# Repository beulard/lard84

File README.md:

# lard84

A custom 75% ansi low-profile keyboard.

- [PCB](#pcb)
- [Plate](#plate)
- [Case](#case)
- [Acknowledgments](#acknowledgments)
- [Extra pictures](#extra-pictures)

The assembly is done in (sort of) [sandwich mount style](https://thomasbaart.nl/2019/04/07/cheat-sheet-custom-keyboard-mounting-styles/).
Compared to sandwich mount, there is no top frame (the plate sits at the top), and
it is screwed into the case's mounting posts from above.

Here it is finally assembled:

## PCB

The PCB (lard84.kicad_pro) is an 84-key design based on the [RP2350 Stamp](https://lectronz.com/products/rp2350-stamp), made using KiCad 8.0.
It is entirely hand-solderable (smallest footprint is 0603).

The design features a micro-usb port, full n-key rollover using a diode for each switch, a status LED, and apparent debug pins for development.

Key placement follows an [ANSI 75% layout](https://docs.keebd.com/information/keyboard-layouts#75-ansi).

The design supports [Gateron KS-33 low-profile switches](https://www.gateron.co/products/gateron-low-profile-mechanical-switch-set), and features holes
for the associated [low-profile stabilizers](https://www.gateron.com/products/gateron-low-profile-plate-mounted-stabilizer).

## Plate

The top plate (plate v38.f3z) supports the switches, adds rigidity and gives a nice finish. It was made in Fusion360.

It is a relatively simple design with a square cutout for each key, two extra cutouts around the Backspace, Space, Enter and LShift keys
for their plate-mounted stabilizers, and 10 mounting holes for screws.

One key challenge was to figure out the placement and shape for the stabilizer cutouts, because of insufficient information on
the datasheets from the manufacturer.

## Case

The case (case.FCStd) is a 3D-printable plastic enclosing and two feet for a more comfortable typing angle.

The enclosing features mounting posts for the PCB and plate, and anti-warping structural elements.

## Acknowledgments

Thanks to these open source repos for providing vital KiCad symbol/footprint libraries.
- [RP2350 Stamp](https://github.com/solderparty/rp2xxx_stamp_footprints)
- [Gateron switches](https://github.com/siderakb/key-switches.pretty)

## Extra pictures

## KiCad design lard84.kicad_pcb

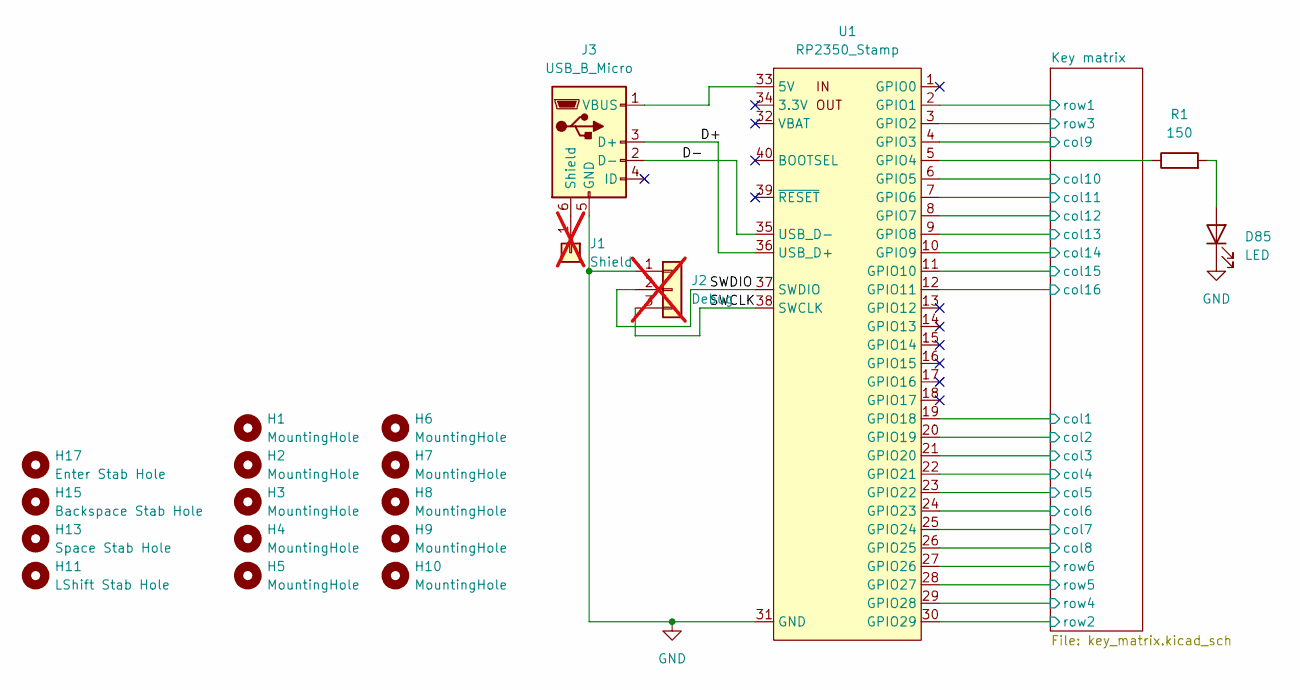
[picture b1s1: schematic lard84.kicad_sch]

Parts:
D85: LED; LED_0603_1608Metric_Pad1.05x0.95mm_HandSolder
H1, H2, H3, H4, H5, H6, H7, H8, H9, H10: MountingHole; Stand hole 5mm
H11: LShift Stab Hole; Gateron low-profile 2U stabilizer
H13: Space Stab Hole; Gateron low-profile 6.25U stabilizer
H15: Backspace Stab Hole; Gateron low-profile 2U stabilizer
H17: Enter Stab Hole; Gateron low-profile 2U stabilizer
J1: Shield; PinSocket_1x01_P2.00mm_Vertical; not fitted
J2: Debug; PinSocket_1x03_P2.54mm_Vertical; not fitted
J3: USB_B_Micro; CONN5_2013499-1_TEC
R1: 150; R_0603_1608Metric_Pad0.98x0.95mm_HandSolder
U1: RP2350_Stamp; RP2xxx_Stamp_SMD

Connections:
/D+: J3.3 (D+), U1.36 (USB_D+)
/D-: J3.2 (D-), U1.35 (USB_D-)
/Key matrix/col1: U1.19 (GPIO18); also elsewhere on the board
/Key matrix/col2: U1.20 (GPIO19); also elsewhere on the board
/Key matrix/col3: U1.21 (GPIO20); also elsewhere on the board
/Key matrix/col4: U1.22 (GPIO21); also elsewhere on the board
/Key matrix/col5: U1.23 (GPIO22); also elsewhere on the board
/Key matrix/col6: U1.24 (GPIO23); also elsewhere on the board
/Key matrix/col7: U1.25 (GPIO24); also elsewhere on the board
/Key matrix/col8: U1.26 (GPIO25); also elsewhere on the board
/Key matrix/col9: U1.4 (GPIO3); also elsewhere on the board
/Key matrix/col10: U1.6 (GPIO5); also elsewhere on the board
/Key matrix/col11: U1.7 (GPIO6); also elsewhere on the board
/Key matrix/col12: U1.8 (GPIO7); also elsewhere on the board
/Key matrix/col13: U1.9 (GPIO8); also elsewhere on the board
/Key matrix/col14: U1.10 (GPIO9); also elsewhere on the board
/Key matrix/col15: U1.11 (GPIO10); also elsewhere on the board
/Key matrix/col16: U1.12 (GPIO11); also elsewhere on the board
/Key matrix/row1: U1.2 (GPIO1); also elsewhere on the board
/Key matrix/row2: U1.30 (GPIO29); also elsewhere on the board
/Key matrix/row3: U1.3 (GPIO2); also elsewhere on the board
/Key matrix/row4: U1.29 (GPIO28); also elsewhere on the board
/Key matrix/row5: U1.28 (GPIO27); also elsewhere on the board
/Key matrix/row6: U1.27 (GPIO26); also elsewhere on the board
/SWCLK: J2.3, U1.38 (SWCLK)
/SWDIO: J2.2, U1.37 (SWDIO)
GND: D85.1 (K), J2.1, J3.5 (GND), U1.31 (GND)
unnamed: D85.2 (A), R1.2
unnamed: J1.1, J3.6 (Shield)
unnamed: J3.1 (VBUS), U1.33 (5V)
unnamed: R1.1, U1.5 (GPIO4)

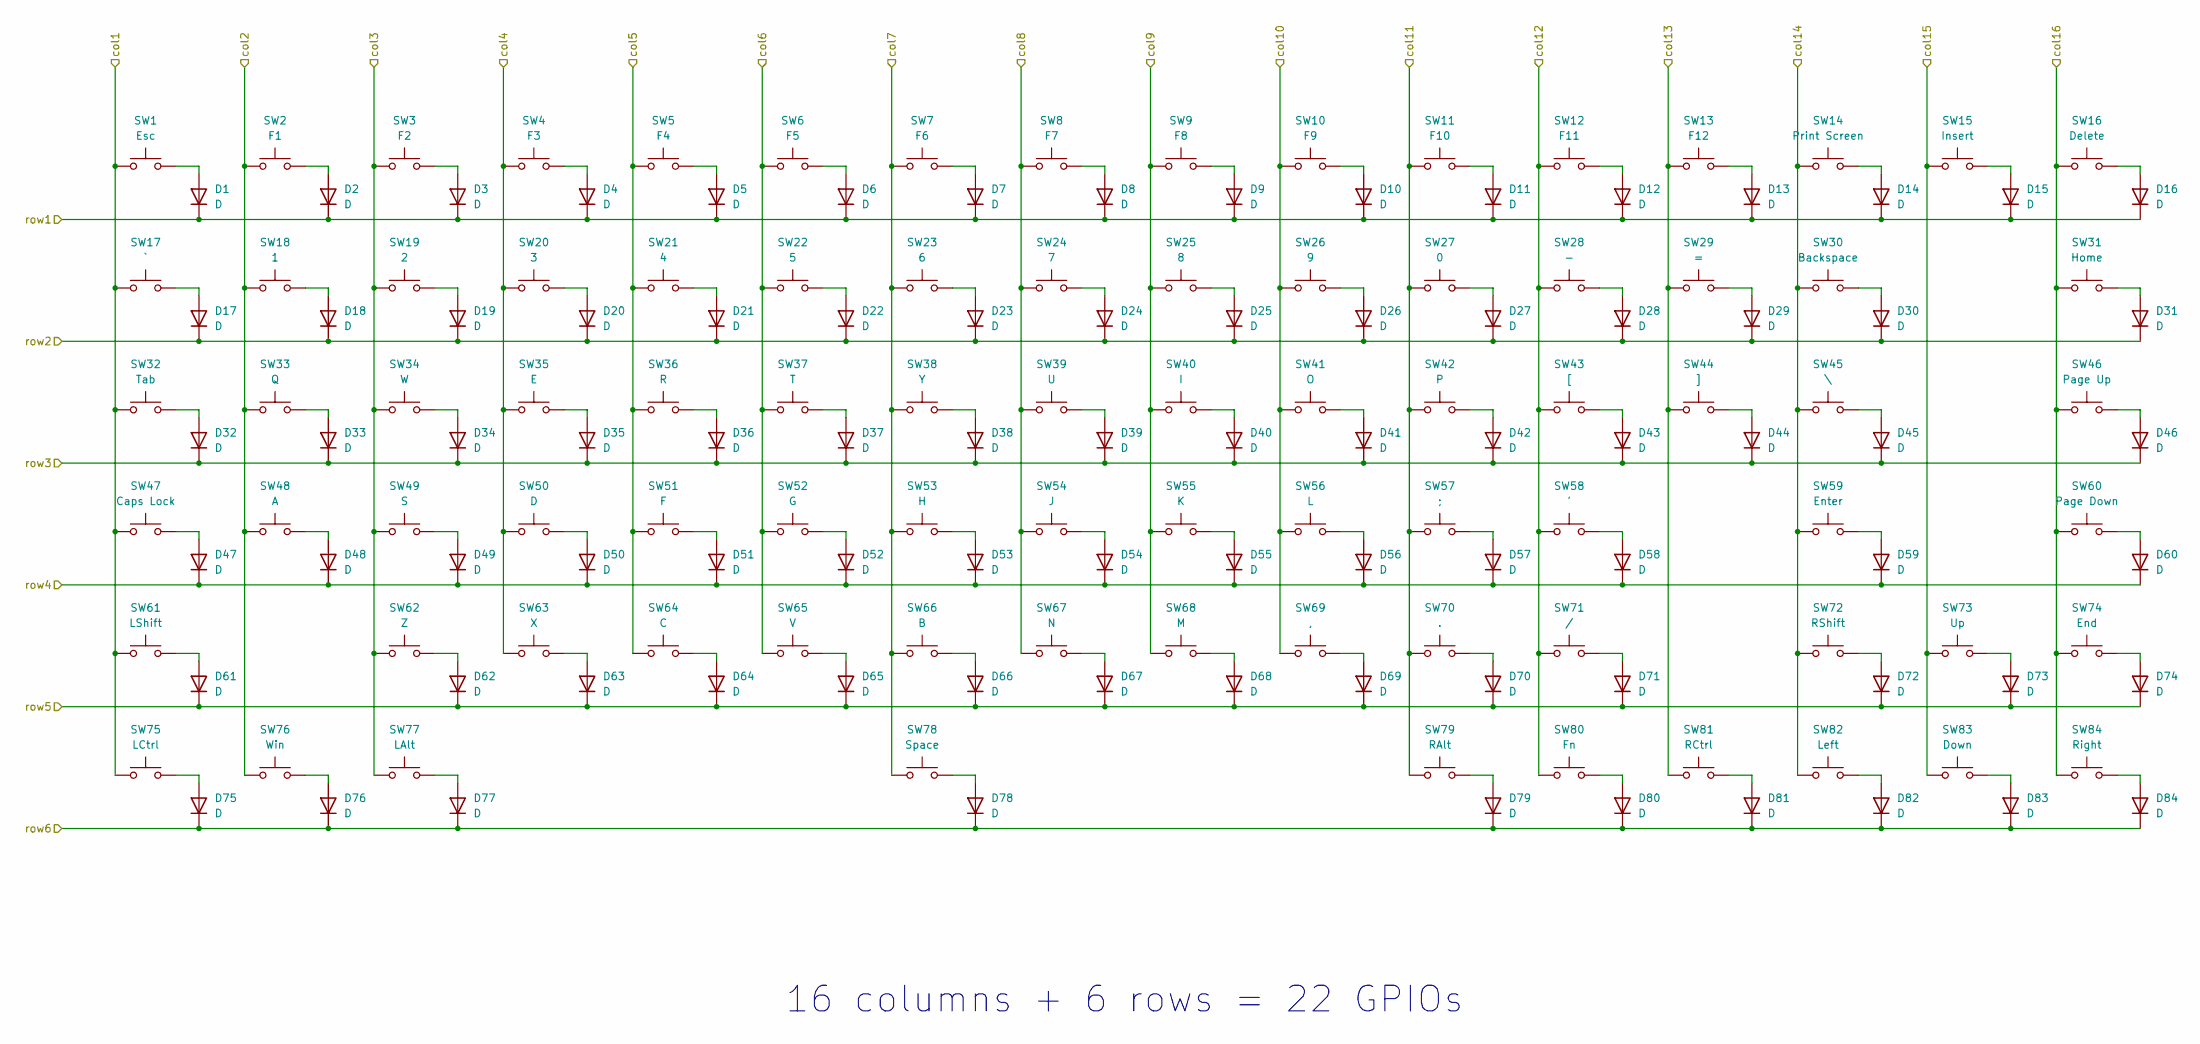
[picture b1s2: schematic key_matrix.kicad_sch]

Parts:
D1, D2, D3, D4, D5, D6, D7, D8, D9, D10, D11, D12, D13, D14, D15, D16, D17, D18, D19, D20, D21, D22, D23, D24, D25, D26, D27, D28, D29, D30, D31, D32, D33, D34, D35, D36, D37, D38, D39, D40, D41, D42, D43, D44, D45, D46, D47, D48, D49, D50, D51, D52, D53, D54, D55, D56, D57, D58, D59, D60, D61, D62, D63, D64, D65, D66, D67, D68, D69, D70, D71, D72, D73, D74, D75, D76, D77, D78, D79, D80, D81, D82, D83, D84: D; D_SOD-123
SW1: Esc; SW_Gateron_LowProfile_THT
SW2: F1; SW_Gateron_LowProfile_THT
SW3: F2; SW_Gateron_LowProfile_THT
SW4: F3; SW_Gateron_LowProfile_THT
SW5: F4; SW_Gateron_LowProfile_THT
SW6: F5; SW_Gateron_LowProfile_THT
SW7: F6; SW_Gateron_LowProfile_THT
SW8: F7; SW_Gateron_LowProfile_THT
SW9: F8; SW_Gateron_LowProfile_THT
SW10: F9; SW_Gateron_LowProfile_THT
SW11: F10; SW_Gateron_LowProfile_THT
SW12: F11; SW_Gateron_LowProfile_THT
SW13: F12; SW_Gateron_LowProfile_THT
SW14: Print Screen; SW_Gateron_LowProfile_THT
SW15: Insert; SW_Gateron_LowProfile_THT
SW16: Delete; SW_Gateron_LowProfile_THT
SW17: `; SW_Gateron_LowProfile_THT
SW18: 1; SW_Gateron_LowProfile_THT
SW19: 2; SW_Gateron_LowProfile_THT
SW20: 3; SW_Gateron_LowProfile_THT
SW21: 4; SW_Gateron_LowProfile_THT
SW22: 5; SW_Gateron_LowProfile_THT
SW23: 6; SW_Gateron_LowProfile_THT
SW24: 7; SW_Gateron_LowProfile_THT
SW25: 8; SW_Gateron_LowProfile_THT
SW26: 9; SW_Gateron_LowProfile_THT
SW27: 0; SW_Gateron_LowProfile_THT
SW28: -; SW_Gateron_LowProfile_THT
SW29: =; SW_Gateron_LowProfile_THT
SW30: Backspace; SW_Gateron_LowProfile_THT
SW31: Home; SW_Gateron_LowProfile_THT
SW32: Tab; SW_Gateron_LowProfile_THT
SW33: Q; SW_Gateron_LowProfile_THT
SW34: W; SW_Gateron_LowProfile_THT
SW35: E; SW_Gateron_LowProfile_THT
SW36: R; SW_Gateron_LowProfile_THT
SW37: T; SW_Gateron_LowProfile_THT
SW38: Y; SW_Gateron_LowProfile_THT
SW39: U; SW_Gateron_LowProfile_THT
SW40: I; SW_Gateron_LowProfile_THT
SW41: O; SW_Gateron_LowProfile_THT
SW42: P; SW_Gateron_LowProfile_THT
SW43: [; SW_Gateron_LowProfile_THT
SW44: ]; SW_Gateron_LowProfile_THT
SW45: \; SW_Gateron_LowProfile_THT
SW46: Page Up; SW_Gateron_LowProfile_THT
SW47: Caps Lock; SW_Gateron_LowProfile_THT
SW48: A; SW_Gateron_LowProfile_THT
SW49: S; SW_Gateron_LowProfile_THT
SW50: D; SW_Gateron_LowProfile_THT
SW51: F; SW_Gateron_LowProfile_THT
SW52: G; SW_Gateron_LowProfile_THT
SW53: H; SW_Gateron_LowProfile_THT
SW54: J; SW_Gateron_LowProfile_THT
SW55: K; SW_Gateron_LowProfile_THT
SW56: L; SW_Gateron_LowProfile_THT
SW57: ;; SW_Gateron_LowProfile_THT
SW58: '; SW_Gateron_LowProfile_THT
SW59: Enter; SW_Gateron_LowProfile_THT
SW60: Page Down; SW_Gateron_LowProfile_THT
SW61: LShift; SW_Gateron_LowProfile_THT
SW62: Z; SW_Gateron_LowProfile_THT
SW63: X; SW_Gateron_LowProfile_THT
SW64: C; SW_Gateron_LowProfile_THT
SW65: V; SW_Gateron_LowProfile_THT
SW66: B; SW_Gateron_LowProfile_THT
SW67: N; SW_Gateron_LowProfile_THT
SW68: M; SW_Gateron_LowProfile_THT
SW69: ,; SW_Gateron_LowProfile_THT
SW70: .; SW_Gateron_LowProfile_THT
SW71: /; SW_Gateron_LowProfile_THT
SW72: RShift; SW_Gateron_LowProfile_THT
SW73: Up; SW_Gateron_LowProfile_THT
SW74: End; SW_Gateron_LowProfile_THT
SW75: LCtrl; SW_Gateron_LowProfile_THT
SW76: Win; SW_Gateron_LowProfile_THT
SW77: LAlt; SW_Gateron_LowProfile_THT
SW78: Space; SW_Gateron_LowProfile_THT
SW79: RAlt; SW_Gateron_LowProfile_THT
SW80: Fn; SW_Gateron_LowProfile_THT
SW81: RCtrl; SW_Gateron_LowProfile_THT
SW82: Left; SW_Gateron_LowProfile_THT
SW83: Down; SW_Gateron_LowProfile_THT
SW84: Right; SW_Gateron_LowProfile_THT

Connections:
/Key matrix/col1: SW1.1, SW17.1, SW32.1, SW47.1, SW61.1, SW75.1; also elsewhere on the board
/Key matrix/col2: SW2.1, SW18.1, SW33.1, SW48.1, SW76.1; also elsewhere on the board
/Key matrix/col3: SW3.1, SW19.1, SW34.1, SW49.1, SW62.1, SW77.1; also elsewhere on the board
/Key matrix/col4: SW4.1, SW20.1, SW35.1, SW50.1, SW63.1; also elsewhere on the board
/Key matrix/col5: SW5.1, SW21.1, SW36.1, SW51.1, SW64.1; also elsewhere on the board
/Key matrix/col6: SW6.1, SW22.1, SW37.1, SW52.1, SW65.1; also elsewhere on the board
/Key matrix/col7: SW7.1, SW23.1, SW38.1, SW53.1, SW66.1, SW78.1; also elsewhere on the board
/Key matrix/col8: SW8.1, SW24.1, SW39.1, SW54.1, SW67.1; also elsewhere on the board
/Key matrix/col9: SW9.1, SW25.1, SW40.1, SW55.1, SW68.1; also elsewhere on the board
/Key matrix/col10: SW10.1, SW26.1, SW41.1, SW56.1, SW69.1; also elsewhere on the board
/Key matrix/col11: SW11.1, SW27.1, SW42.1, SW57.1, SW70.1, SW79.1; also elsewhere on the board
/Key matrix/col12: SW12.1, SW28.1, SW43.1, SW58.1, SW71.1, SW80.1; also elsewhere on the board
/Key matrix/col13: SW13.1, SW29.1, SW44.1, SW81.1; also elsewhere on the board
/Key matrix/col14: SW14.1, SW30.1, SW45.1, SW59.1, SW72.1, SW82.1; also elsewhere on the board
/Key matrix/col15: SW15.1, SW73.1, SW83.1; also elsewhere on the board
/Key matrix/col16: SW16.1, SW31.1, SW46.1, SW60.1, SW74.1, SW84.1; also elsewhere on the board
/Key matrix/row1: D1.1 (K), D2.1 (K), D3.1 (K), D4.1 (K), D5.1 (K), D6.1 (K), D7.1 (K), D8.1 (K), D9.1 (K), D10.1 (K), D11.1 (K), D12.1 (K), D13.1 (K), D14.1 (K), D15.1 (K), D16.1 (K); also elsewhere on the board
/Key matrix/row2: D17.1 (K), D18.1 (K), D19.1 (K), D20.1 (K), D21.1 (K), D22.1 (K), D23.1 (K), D24.1 (K), D25.1 (K), D26.1 (K), D27.1 (K), D28.1 (K), D29.1 (K), D30.1 (K), D31.1 (K); also elsewhere on the board
/Key matrix/row3: D32.1 (K), D33.1 (K), D34.1 (K), D35.1 (K), D36.1 (K), D37.1 (K), D38.1 (K), D39.1 (K), D40.1 (K), D41.1 (K), D42.1 (K), D43.1 (K), D44.1 (K), D45.1 (K), D46.1 (K); also elsewhere on the board
/Key matrix/row4: D47.1 (K), D48.1 (K), D49.1 (K), D50.1 (K), D51.1 (K), D52.1 (K), D53.1 (K), D54.1 (K), D55.1 (K), D56.1 (K), D57.1 (K), D58.1 (K), D59.1 (K), D60.1 (K); also elsewhere on the board
/Key matrix/row5: D61.1 (K), D62.1 (K), D63.1 (K), D64.1 (K), D65.1 (K), D66.1 (K), D67.1 (K), D68.1 (K), D69.1 (K), D70.1 (K), D71.1 (K), D72.1 (K), D73.1 (K), D74.1 (K); also elsewhere on the board
/Key matrix/row6: D75.1 (K), D76.1 (K), D77.1 (K), D78.1 (K), D79.1 (K), D80.1 (K), D81.1 (K), D82.1 (K), D83.1 (K), D84.1 (K); also elsewhere on the board
unnamed: D1.2 (A), SW1.2
unnamed: D2.2 (A), SW2.2
unnamed: D3.2 (A), SW3.2
unnamed: D4.2 (A), SW4.2
unnamed: D5.2 (A), SW5.2
unnamed: D6.2 (A), SW6.2
unnamed: D7.2 (A), SW7.2
unnamed: D8.2 (A), SW8.2
unnamed: D9.2 (A), SW9.2
unnamed: D10.2 (A), SW10.2
unnamed: D11.2 (A), SW11.2
unnamed: D12.2 (A), SW12.2
unnamed: D13.2 (A), SW13.2
unnamed: D14.2 (A), SW14.2
unnamed: D15.2 (A), SW15.2
unnamed: D16.2 (A), SW16.2
unnamed: D17.2 (A), SW17.2
unnamed: D18.2 (A), SW18.2
unnamed: D19.2 (A), SW19.2
unnamed: D20.2 (A), SW20.2
unnamed: D21.2 (A), SW21.2
unnamed: D22.2 (A), SW22.2
unnamed: D23.2 (A), SW23.2
unnamed: D24.2 (A), SW24.2
unnamed: D25.2 (A), SW25.2
unnamed: D26.2 (A), SW26.2
unnamed: D27.2 (A), SW27.2
unnamed: D28.2 (A), SW28.2
unnamed: D29.2 (A), SW29.2
unnamed: D30.2 (A), SW30.2
unnamed: D31.2 (A), SW31.2
unnamed: D32.2 (A), SW32.2
unnamed: D33.2 (A), SW33.2
unnamed: D34.2 (A), SW34.2
unnamed: D35.2 (A), SW35.2
unnamed: D36.2 (A), SW36.2
unnamed: D37.2 (A), SW37.2
unnamed: D38.2 (A), SW38.2
unnamed: D39.2 (A), SW39.2
unnamed: D40.2 (A), SW40.2
unnamed: D41.2 (A), SW41.2
unnamed: D42.2 (A), SW42.2
unnamed: D43.2 (A), SW43.2
unnamed: D44.2 (A), SW44.2
unnamed: D45.2 (A), SW45.2
unnamed: D46.2 (A), SW46.2
unnamed: D47.2 (A), SW47.2
unnamed: D48.2 (A), SW48.2
unnamed: D49.2 (A), SW49.2
unnamed: D50.2 (A), SW50.2
unnamed: D51.2 (A), SW51.2
unnamed: D52.2 (A), SW52.2
unnamed: D53.2 (A), SW53.2
unnamed: D54.2 (A), SW54.2
unnamed: D55.2 (A), SW55.2
unnamed: D56.2 (A), SW56.2
unnamed: D57.2 (A), SW57.2
unnamed: D58.2 (A), SW58.2
unnamed: D59.2 (A), SW59.2
unnamed: D60.2 (A), SW60.2
unnamed: D61.2 (A), SW61.2
unnamed: D62.2 (A), SW62.2
unnamed: D63.2 (A), SW63.2
unnamed: D64.2 (A), SW64.2
unnamed: D65.2 (A), SW65.2
unnamed: D66.2 (A), SW66.2
unnamed: D67.2 (A), SW67.2
unnamed: D68.2 (A), SW68.2
unnamed: D69.2 (A), SW69.2
unnamed: D70.2 (A), SW70.2
unnamed: D71.2 (A), SW71.2
unnamed: D72.2 (A), SW72.2
unnamed: D73.2 (A), SW73.2
unnamed: D74.2 (A), SW74.2
unnamed: D75.2 (A), SW75.2
unnamed: D76.2 (A), SW76.2
unnamed: D77.2 (A), SW77.2
unnamed: D78.2 (A), SW78.2
unnamed: D79.2 (A), SW79.2
unnamed: D80.2 (A), SW80.2
unnamed: D81.2 (A), SW81.2
unnamed: D82.2 (A), SW82.2
unnamed: D83.2 (A), SW83.2
unnamed: D84.2 (A), SW84.2

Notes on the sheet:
16 columns + 6 rows = 22 GPIOs

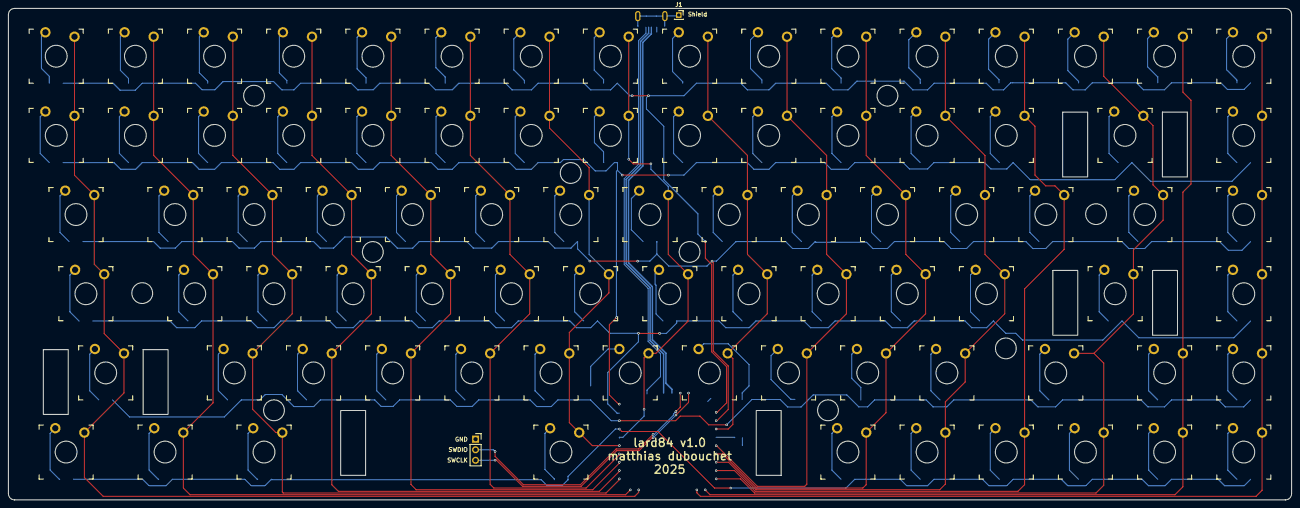
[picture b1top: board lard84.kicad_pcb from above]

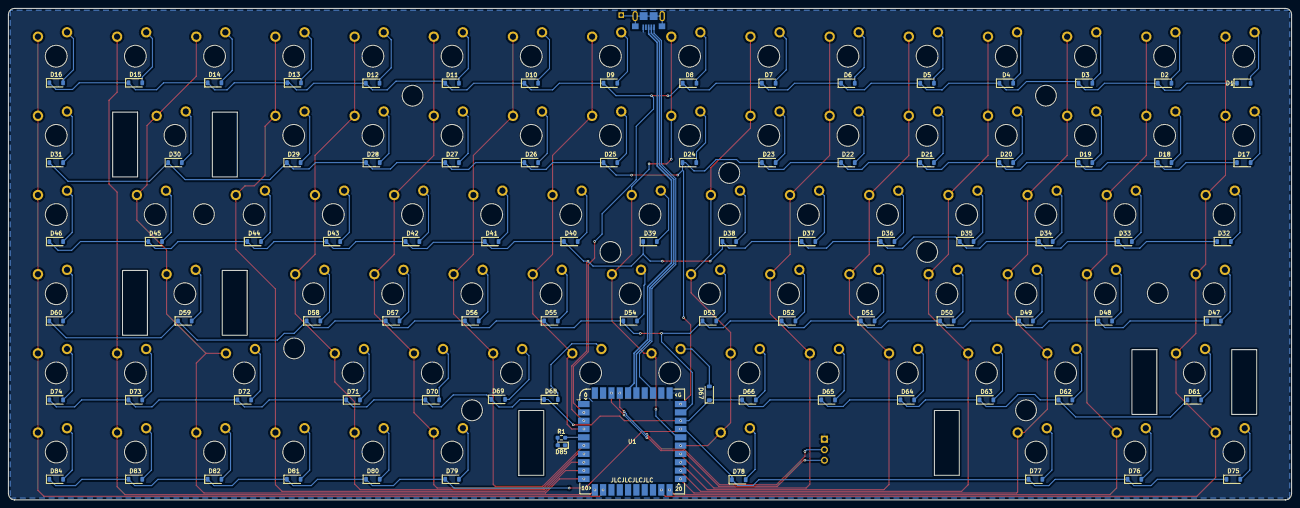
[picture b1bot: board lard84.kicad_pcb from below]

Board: 2 copper layers, 308.7 x 118.2 mm, 188 parts (88 on the bottom side), 115 nets.

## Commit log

2025-02-27 Add KiCad project files
2025-02-27 75% layout
2025-02-27 Schematic printout
2025-02-27 PCB layout printout
2025-02-27 v1.0 screenshots
2025-02-27 Add README
2025-05-01 Fix missing keymatrix schematic
2025-05-01 Add plate, case screenshots
2025-05-01 Add case source file
2025-05-01 Add plate and case info
2025-05-01 Add plate source file
2025-05-01 Add pics
2025-05-01 More info and pics
2025-05-01 Improve descriptions
2025-05-01 Adjust exposure
2025-05-26 Add assembled pics
